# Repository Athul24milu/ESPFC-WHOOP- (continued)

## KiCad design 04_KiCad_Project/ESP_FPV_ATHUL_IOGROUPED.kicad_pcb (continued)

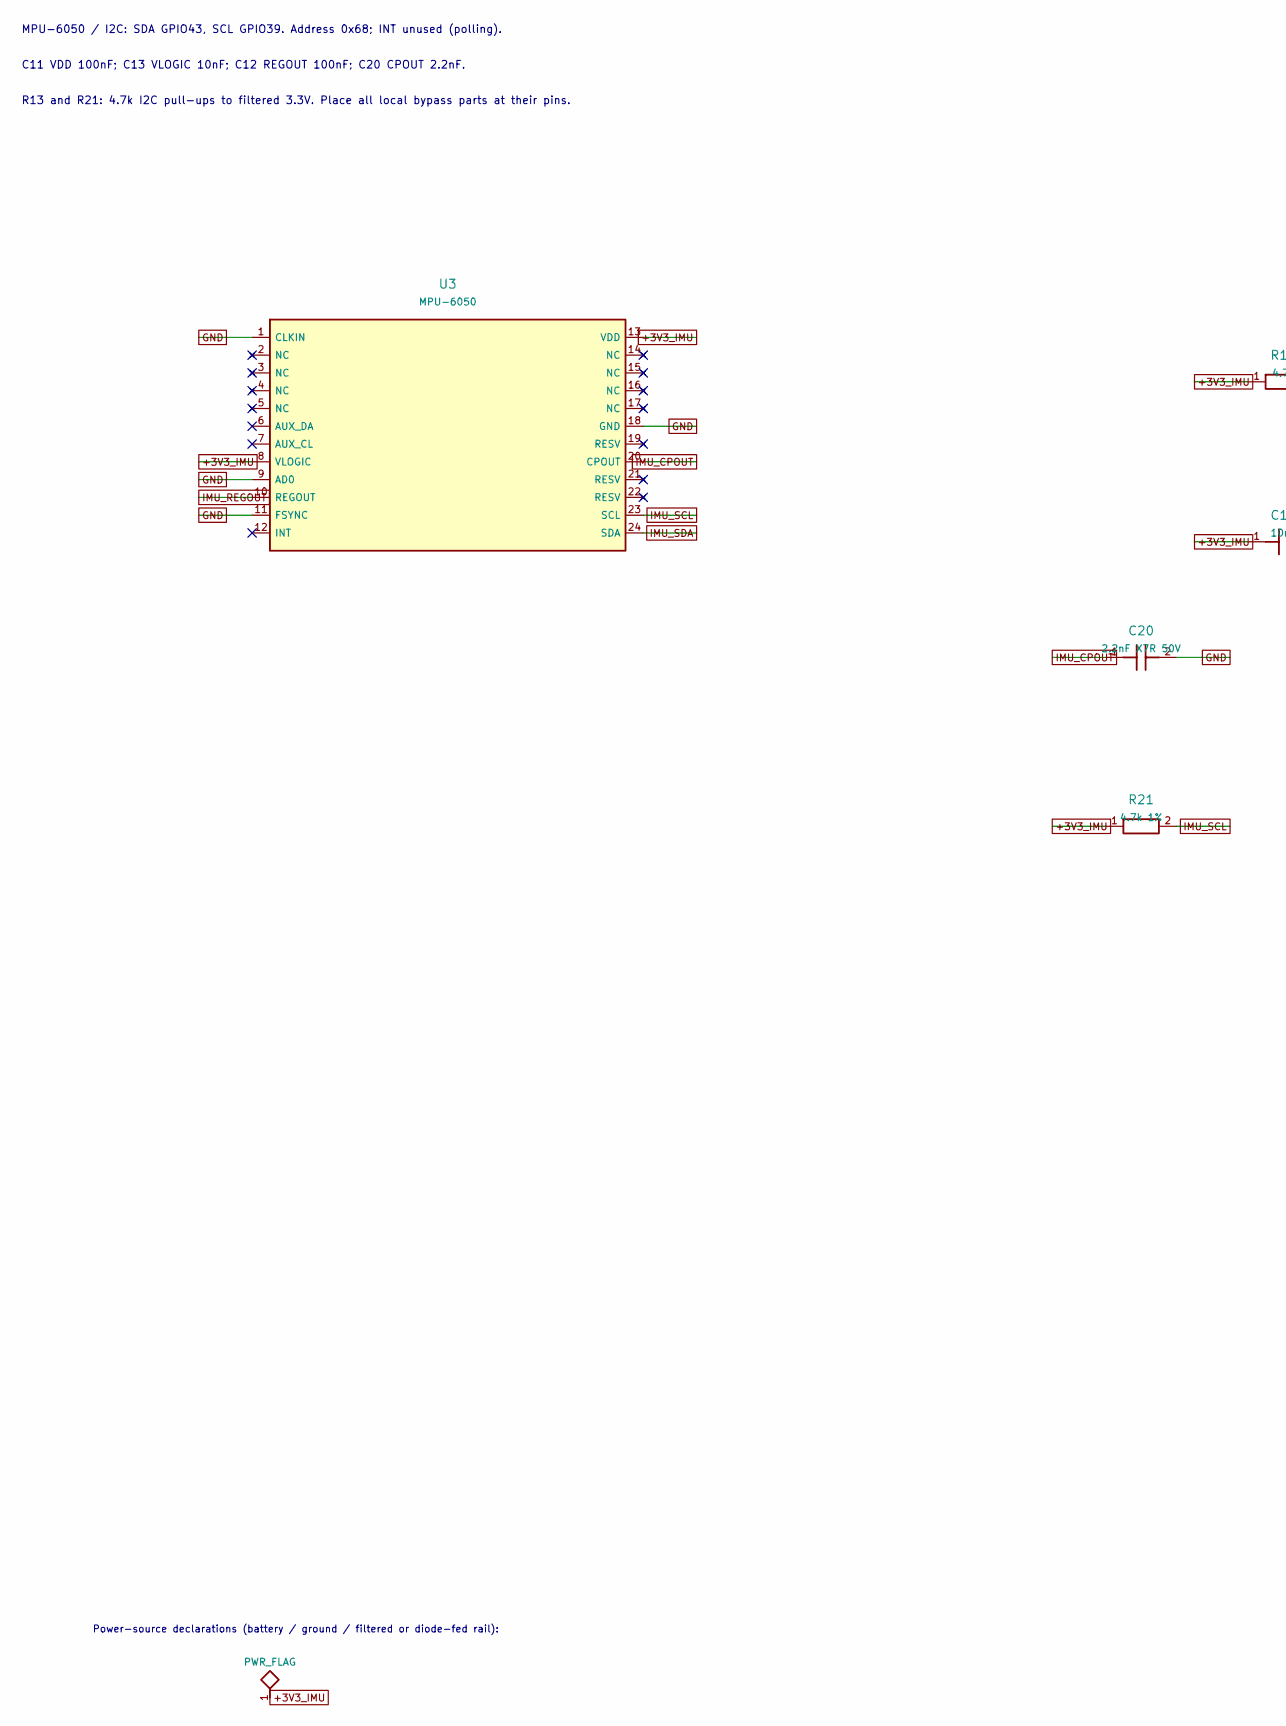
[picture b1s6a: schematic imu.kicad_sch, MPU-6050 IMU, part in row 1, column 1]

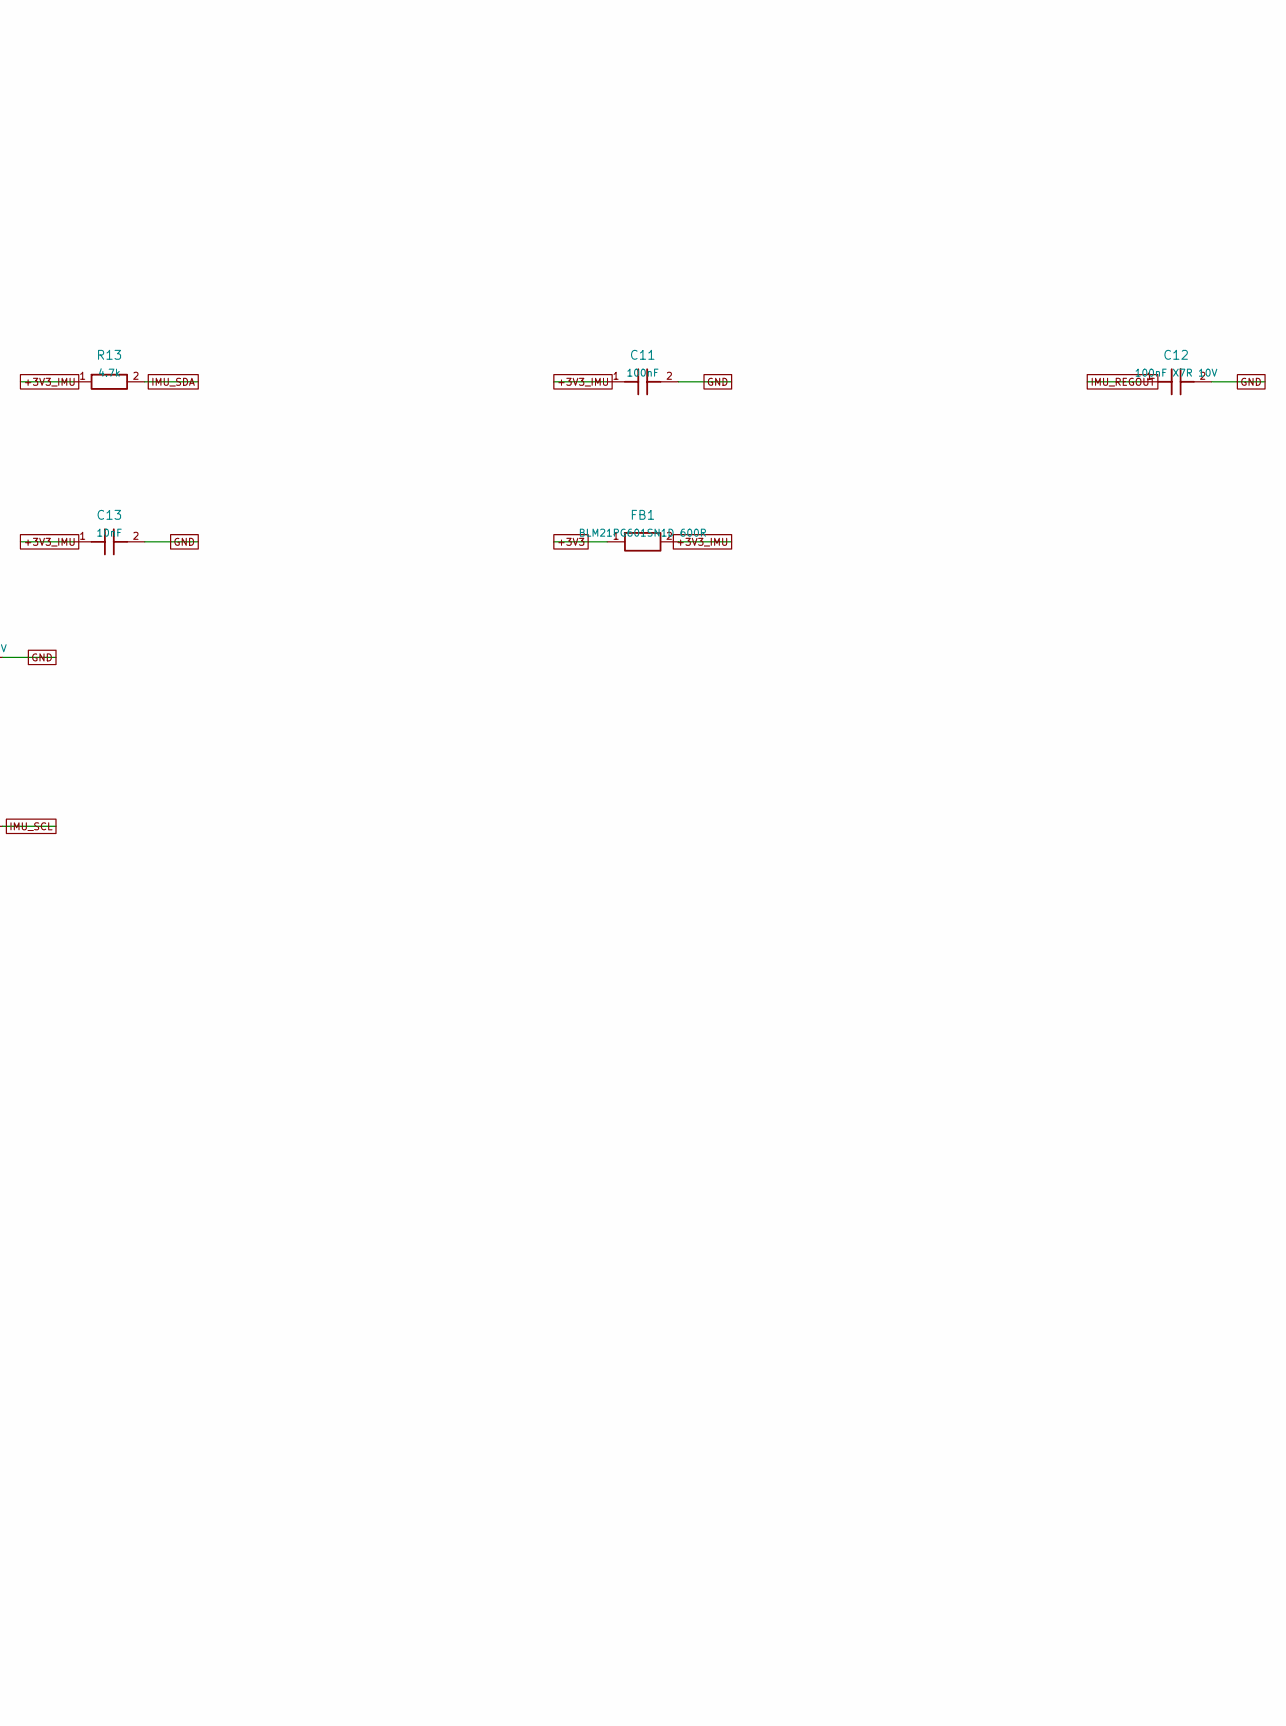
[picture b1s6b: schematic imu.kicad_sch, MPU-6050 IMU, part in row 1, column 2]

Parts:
C11: 100nF; C_0805_2012Metric_Compact
C12: 100nF X7R 10V; C_0805_2012Metric_Compact
C13: 10nF; C_0805_2012Metric_Compact
C20: 2.2nF X7R 50V; RevK_Assembly_C20
FB1: BLM21PG601SN1D 600R; L_0805_2012Metric_Compact
R13: 4.7k; R_0805_2012Metric_Compact
R21: 4.7k 1%; R_0805_2012Metric_Compact
U3: MPU-6050; RevK_Assembly_U3

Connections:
+3V3: FB1.1; also elsewhere on the board
+3V3_IMU: C11.1, C13.1, FB1.2, R13.1, R21.1, U3.8 (VLOGIC), U3.13 (VDD)
GND: C11.2, C12.2, C13.2, C20.2, U3.1 (CLKIN), U3.9 (AD0), U3.11 (FSYNC), U3.18 (GND); also elsewhere on the board
IMU_CPOUT: C20.1, U3.20 (CPOUT)
IMU_REGOUT: C12.1, U3.10 (REGOUT)
IMU_SCL: R21.2, U3.23 (SCL); also elsewhere on the board
IMU_SDA: R13.2, U3.24 (SDA); also elsewhere on the board

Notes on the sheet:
Power-source declarations (battery / ground / filtered or diode-fed rail):
MPU-6050 / I2C: SDA GPIO43, SCL GPIO39. Address 0x68; INT unused (polling).
C11 VDD 100nF; C13 VLOGIC 10nF; C12 REGOUT 100nF; C20 CPOUT 2.2nF.
R13 and R21: 4.7k I2C pull-ups to filtered 3.3V. Place all local bypass parts at their pins.

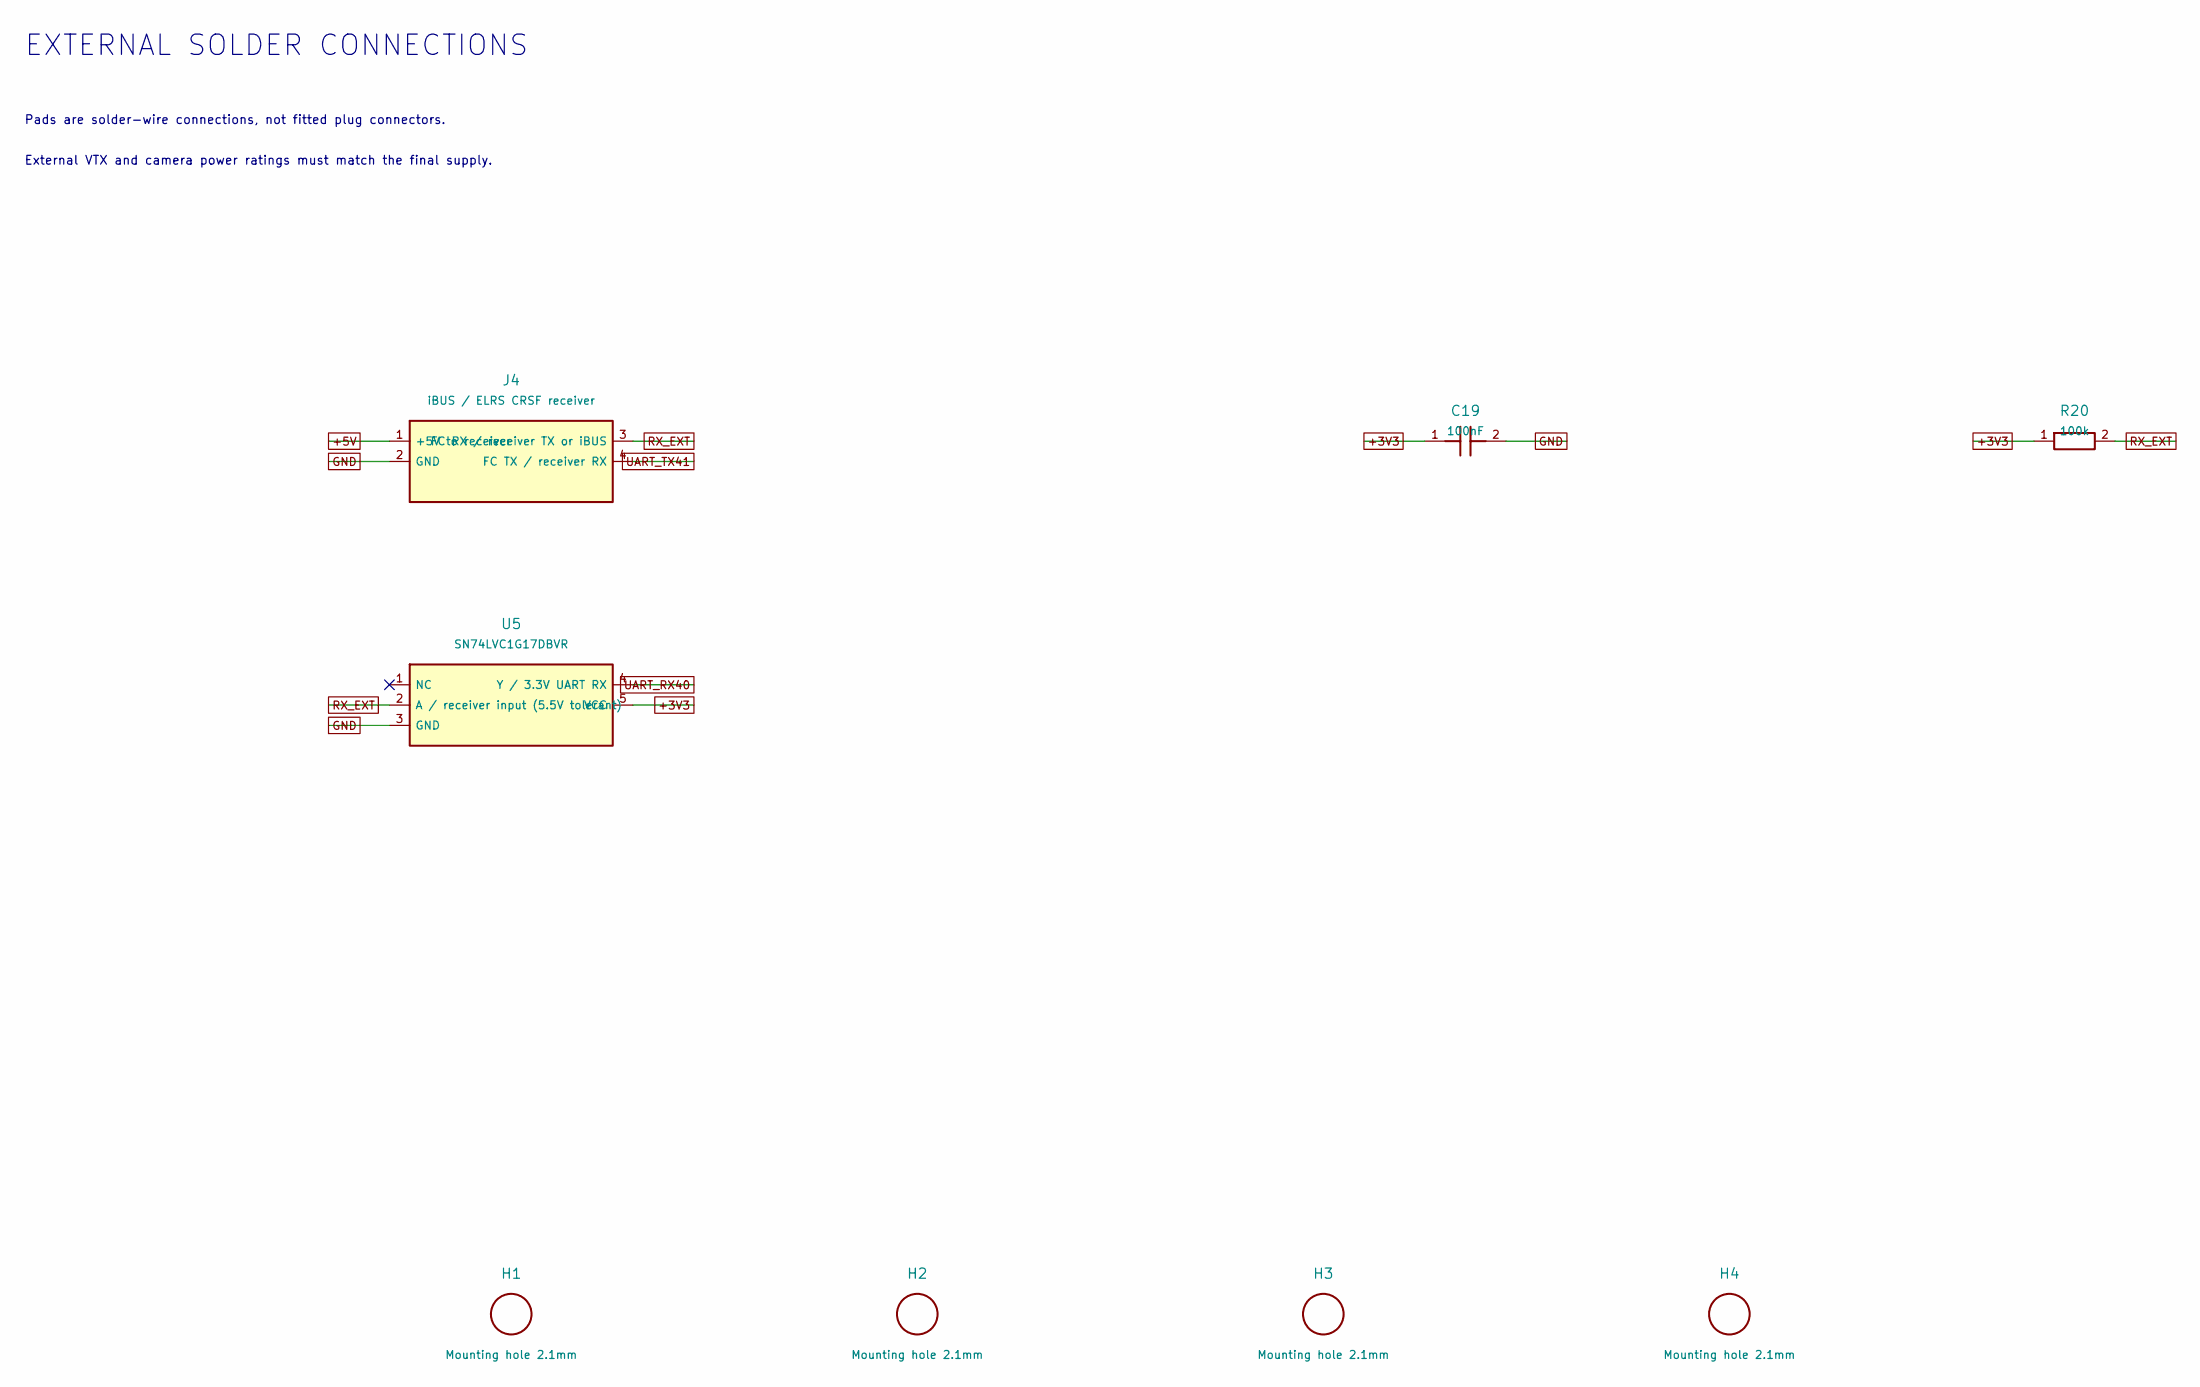
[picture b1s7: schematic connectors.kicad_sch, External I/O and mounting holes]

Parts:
C19: 100nF; C_0805_2012Metric_Compact
H1, H2, H3, H4: Mounting hole 2.1mm; Hole_2p1mm_3p6Head
J4: iBUS / ELRS CRSF receiver; Receiver_Pads_1p5
R20: 100k; R_0805_2012Metric_Compact
U5: SN74LVC1G17DBVR; Receiver_Buffer_SOT23_5

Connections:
+3V3: C19.1, R20.1, U5.5 (VCC); also elsewhere on the board
+5V: J4.1 (+5V to receiver); also elsewhere on the board
GND: C19.2, J4.2 (GND), U5.3 (GND); also elsewhere on the board
RX_EXT: J4.3 (FC RX / receiver TX or iBUS), R20.2, U5.2 (A / receiver input (5.5V tolerant))
UART_RX40: U5.4 (Y / 3.3V UART RX); also elsewhere on the board
UART_TX41: J4.4 (FC TX / receiver RX); also elsewhere on the board

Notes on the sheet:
EXTERNAL SOLDER CONNECTIONS
Pads are solder-wire connections, not fitted plug connectors.
External VTX and camera power ratings must match the final supply.

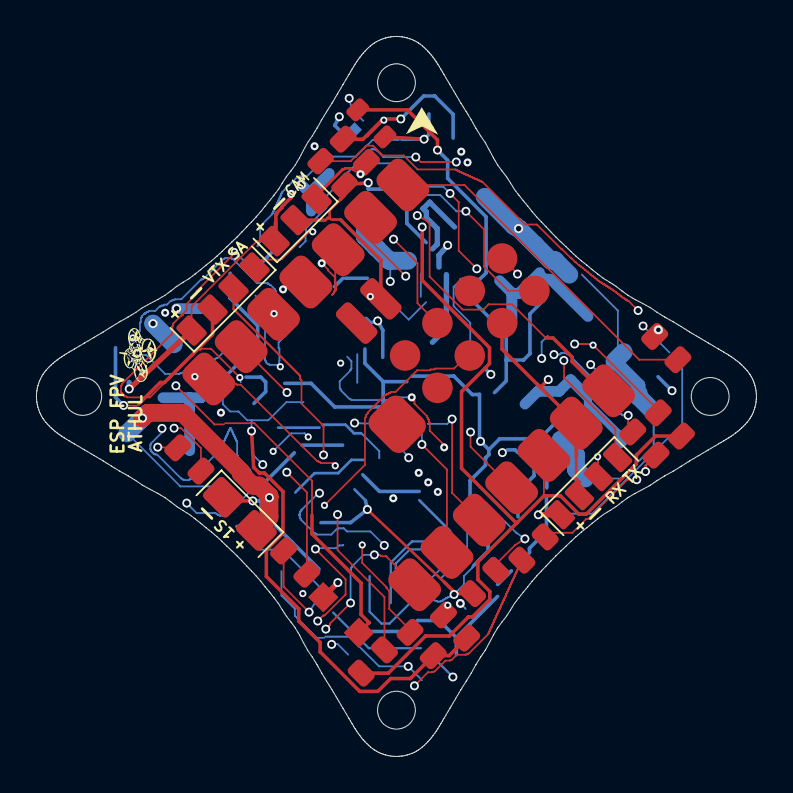
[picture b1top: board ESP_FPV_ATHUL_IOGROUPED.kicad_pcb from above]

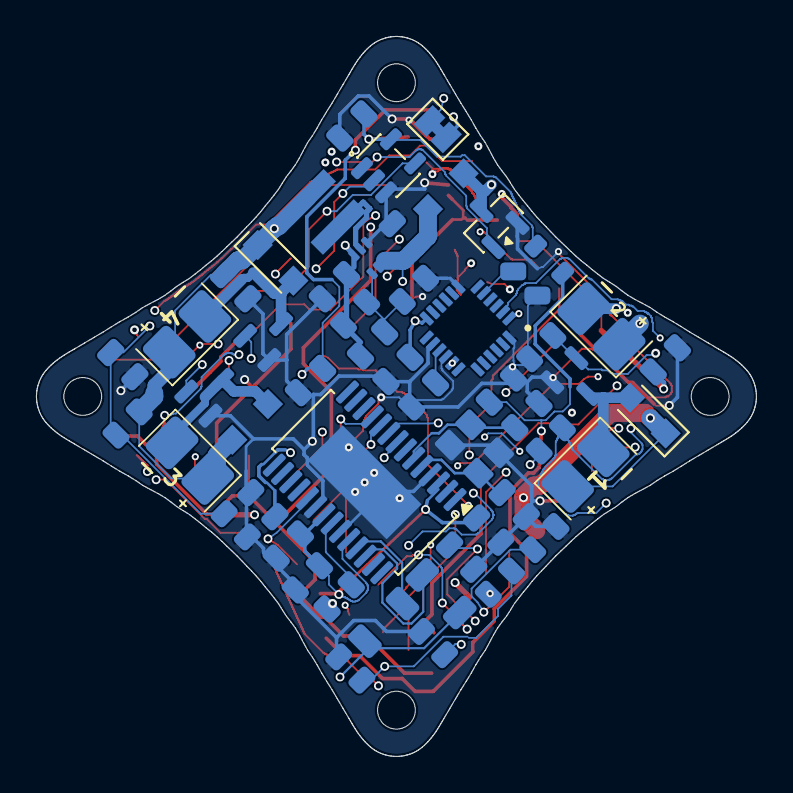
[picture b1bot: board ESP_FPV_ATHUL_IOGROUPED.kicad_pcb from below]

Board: 4 copper layers, 40.0 x 40.0 mm, 75 parts (52 on the bottom side), 47 nets.

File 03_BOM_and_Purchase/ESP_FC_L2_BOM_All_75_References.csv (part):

Reference,Qty per FC,Value,Package,Side,Fit,Purchase status,Product or catalogue link,Robu search,Quartz search,Evelta search,Notes,Data date
C1,1,100nF,0805,bottom,FIT,Matching listing found; confirm stock at checkout,https://quartzcomponents.com/products/kemet-100nf-50v-0805-s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,https://robu.in/?s=100nF%200805&post_type=product,https://quartzcomponents.com/search?q=100nF%200805&type=product,https://evelta.com/search.php?search_query=100nF%200805,"Ceramic, non-polarized. Use X7R, >=10V (50V acceptable).",2026-11-10
C2,1,100nF,0805,bottom,FIT,Matching listing found; confirm stock at checkout,https://quartzcomponents.com/products/kemet-100nf-50v-0805-s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,https://robu.in/?s=100nF%200805&post_type=product,https://quartzcomponents.com/search?q=100nF%200805&type=product,https://evelta.com/search.php?search_query=100nF%200805,"Ceramic, non-polarized. Use X7R, >=10V (50V acceptable).",2026-11-10
C3,1,100nF,0805,bottom,FIT,Matching listing found; confirm stock at checkout,https://quartzcomponents.com/products/kemet-100nf-50v-0805-s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,https://robu.in/?s=100nF%200805&post_type=product,https://quartzcomponents.com/search?q=100nF%200805&type=product,https://evelta.com/search.php?search_query=100nF%200805,"Ceramic, non-polarized. Use X7R, >=10V (50V acceptable).",2026-11-10
C4,1,100nF,0805,bottom,FIT,Matching listing found; confirm stock at checkout,https://quartzcomponents.com/products/kemet-100nf-50v-0805-s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,https://robu.in/?s=100nF%200805&post_type=product,https://quartzcomponents.com/search?q=100nF%200805&type=product,https://evelta.com/search.php?search_query=100nF%200805,"Ceramic, non-polarized. Use X7R, >=10V (50V acceptable).",2026-11-10
C5,1,100nF,0805,bottom,FIT,Matching listing found; confirm stock at checkout,https://quartzcomponents.com/products/kemet-100nf-50v-0805-s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,https://robu.in/?s=100nF%200805&post_type=product,https://quartzcomponents.com/search?q=100nF%200805&type=product,https://evelta.com/search.php?search_query=100nF%200805,"Ceramic, non-polarized. Use X7R, >=10V (50V acceptable).",2026-11-10
C6,1,47uF 10V X5R,1206,bottom,FIT,Search links only; exact orderable SKU not confirmed,,https://robu.in/?s=47uF%2010V%20X5R%201206&post_type=product,https://quartzcomponents.com/search?q=47uF%2010V%20X5R%20120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,https://evelta.com/search.php?search_query=47uF%2010V%20X5R%201206,"Ceramic, non-polarized. Match dielectric and voltage shown; check effective capacitance under bias.",2026-11-10
C7,1,47uF 10V X5R,1206,bottom,FIT,Search links only; exact orderable SKU not confirmed,,https://robu.in/?s=47uF%2010V%20X5R%201206&post_type=product,https://quartzcomponents.com/search?q=47uF%2010V%20X5R%20120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,https://evelta.com/search.php?search_query=47uF%2010V%20X5R%201206,"Ceramic, non-polarized. Match dielectric and voltage shown; check effective capacitance under bias.",2026-11-10
C8,1,10uF 10V X5R,0805,bottom,FIT,Search links only; exact orderable SKU not confirmed,,https://robu.in/?s=10uF%2010V%20X5R%200805&post_type=product,https://quartzcomponents.com/search?q=10uF%2010V%20X5R%20080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,https://evelta.com/search.php?search_query=10uF%2010V%20X5R%200805,"Ceramic, non-polarized. Match dielectric and voltage shown; check effective capacitance under bias.",2026-11-10
C9,1,100nF,0805,bottom,FIT,Matching listing found; confirm stock at checkout,https://quartzcomponents.com/products/kemet-100nf-50v-0805-s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,https://robu.in/?s=100nF%200805&post_type=product,https://quartzcomponents.com/search?q=100nF%200805&type=product,https://evelta.com/search.php?search_query=100nF%200805,"Ceramic, non-polarized. Use X7R, >=10V (50V acceptable).",2026-11-10
C10,1,100nF,0805,bottom,FIT,Matching listing found; confirm stock at checkout,https://quartzcomponents.com/products/kemet-100nf-50v-0805-s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,https://robu.in/?s=100nF%200805&post_type=product,https://quartzcomponents.com/search?q=100nF%200805&type=product,https://evelta.com/search.php?search_query=100nF%200805,"Ceramic, non-polarized. Use X7R, >=10V (50V acceptable).",2026-11-10
C11,1,100nF,0805,bottom,FIT,Matching listing found; confirm stock at checkout,https://quartzcomponents.com/products/kemet-100nf-50v-0805-s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,https://robu.in/?s=100nF%200805&post_type=product,https://quartzcomponents.com/search?q=100nF%200805&type=product,https://evelta.com/search.php?search_query=100nF%200805,"Ceramic, non-polarized. Use X7R, >=10V (50V acceptable).",2026-11-10
C12,1,100nF X7R 10V,0805,bottom,FIT,Search links only; exact orderable SKU not confirmed,,https://robu.in/?s=100nF%20X7R%2010V%200805&post_type=product,https://quartzcomponents.com/search?q=100nF%20X7R%2010V%2008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,https://evelta.com/search.php?search_query=100nF%20X7R%2010V%200805,"Ceramic, non-polarized. Use X7R, >=10V (50V acceptable).",2026-11-10
C13,1,10nF,0805,bottom,FIT,Search links only; exact orderable SKU not confirmed,,https://robu.in/?s=10nF%200805&post_type=product,https://quartzcomponents.com/search?q=10nF%200805&type=product,https://evelta.com/search.php?search_query=10nF%200805,"Ceramic, non-polarized. Use X7R, >=10V (50V acceptable).",2026-11-10
C14,1,10uF 10V X5R,0805,bottom,FIT,Search links only; exact orderable SKU not confirmed,,https://robu.in/?s=10uF%2010V%20X5R%200805&post_type=product,https://quartzcomponents.com/search?q=10uF%2010V%20X5R%20080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,https://evelta.com/search.php?search_query=10uF%2010V%20X5R%200805,"Ceramic, non-polarized. Match dielectric and voltage shown; check effective capacitance under bias.",2026-11-10
C15,1,22uF 10V X5R,0805,bottom,FIT,Search links only; exact orderable SKU not confirmed,,https://robu.in/?s=22uF%2010V%20X5R%200805&post_type=product,https://quartzcomponents.com/search?q=22uF%2010V%20X5R%20080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,https://evelta.com/search.php?search_query=22uF%2010V%20X5R%200805,"Ceramic, non-polarized. Match dielectric and voltage shown; check effective capacitance under bias.",2026-11-10
C16,1,22uF 10V X5R,0805,bottom,FIT,Search links only; exact orderable SKU not confirmed,,https://robu.in/?s=22uF%2010V%20X5R%200805&post_type=product,https://quartzcomponents.com/search?q=22uF%2010V%20X5R%20080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,https://evelta.com/search.php?search_query=22uF%2010V%20X5R%200805,"Ceramic, non-polarized. Match dielectric and voltage shown; check effective capacitance under bias.",2026-11-10
C17,1,220pF C0G,0805,bottom,FIT,C0G 220pF listing found in Quartz catalogue; confirm stock,https://quartzcomponents.com/collections/smd-capacitors?page=3,https://robu.in/?s=220pF%20C0G%200805&post_type=product,https://quartzcomponents.com/search?q=220pF%20C0G%200805&typ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,https://evelta.com/search.php?search_query=220pF%20C0G%200805,"FIT in L2, 0805 220pF C0G/NP0; NOT DNP. Catalogue link, not a direct item page.",2026-11-10
C18,1,22uF 10V X5R,0805,bottom,FIT,Search links only; exact orderable SKU not confirmed,,https://robu.in/?s=22uF%2010V%20X5R%200805&post_type=product,https://quartzcomponents.com/search?q=22uF%2010V%20X5R%20080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,https://evelta.com/search.php?search_query=22uF%2010V%20X5R%200805,"Ceramic, non-polarized. Match dielectric and voltage shown; check effective capacitance under bias.",2026-11-10
C19,1,100nF,0805,bottom,FIT,Matching listing found; confirm stock at checkout,https://quartzcomponents.com/products/kemet-100nf-50v-0805-s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,https://robu.in/?s=100nF%200805&post_type=product,https://quartzcomponents.com/search?q=100nF%200805&type=product,https://evelta.com/search.php?search_query=100nF%200805,"Ceramic, non-polarized. Use X7R, >=10V (50V acceptable).",2026-11-10
C20,1,2.2nF X7R 50V,0805,bottom,FIT,Prior product candidate; current stock unconfirmed,https://quartzcomponents.com/products/kemet-2-2nf-50v-805-sm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,https://robu.in/?s=2.2nF%20X7R%2050V%200805&post_type=product,https://quartzcomponents.com/search?q=2.2nF%20X7R%2050V%2008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,https://evelta.com/search.php?search_query=2.2nF%20X7R%2050V%200805,0805 2.2nF X7R 50V; Kemet C0805C222K5RACTU. URL says C0G: require shipped MPN/dielectric confirmation.,2026-11-10
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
